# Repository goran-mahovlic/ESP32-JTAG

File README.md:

# ESP32-JTAG

ESP32 on simple board that can be used for JTAG

I use micropython code for programming FPGA 

https://github.com/emard/esp32ecp5

ESP32 connections are pulled out of ULX3S board to have stand alone board.

https://github.com/emard/ulx3s

https://www.hackster.io/news/the-esp32-is-the-chip-that-keeps-on-giving-this-time-as-a-wi-fi-jtag-programmer-for-the-ecp5-1319c7570c01

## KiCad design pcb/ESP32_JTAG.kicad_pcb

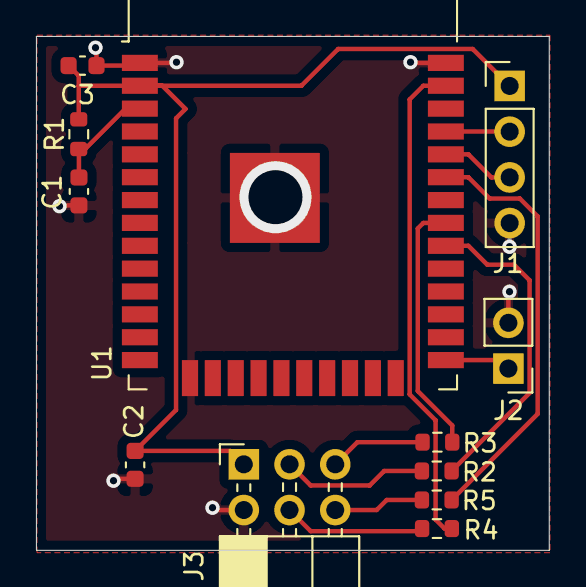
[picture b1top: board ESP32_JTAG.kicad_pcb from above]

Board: 2 copper layers, 28.5 x 28.6 mm, 12 parts (0 on the bottom side), 14 nets.

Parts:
C1, C2, C3: C; C_0603_1608Metric
J1: FLASH; PinHeader_1x04_P2.54mm_Vertical
J2: BOOT; PinHeader_1x02_P2.54mm_Vertical
J3: JTAG; PinSocket_2x03_P2.54mm_Horizontal
R1: 4K7; R_0603_1608Metric
R2, R3, R4, R5: 200; R_0603_1608Metric
U1: ESP32-WROOM-32

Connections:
+3V3: C2.1, C3.1, J1.1, J3.1, R1.1, U1.2
BOOT: J2.1, U1.25
GND: C1.2, C2.2, C3.2, J1.4, J2.2, J3.2, U1.1, U1.15, U1.38, U1.39
unnamed: C1.1, R1.2, U1.3
unnamed: J3.3, R2.1
unnamed: J3.4, R4.2
unnamed: J3.5, R3.1
unnamed: J3.6, R5.2
RX: J1.2, U1.35
TCK: R2.2, U1.30
TDI: R4.1, U1.37
TDO: R3.2, U1.31
TMS: R5.1, U1.33
TX: J1.3, U1.34

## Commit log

2021-02-28 Inititial version
